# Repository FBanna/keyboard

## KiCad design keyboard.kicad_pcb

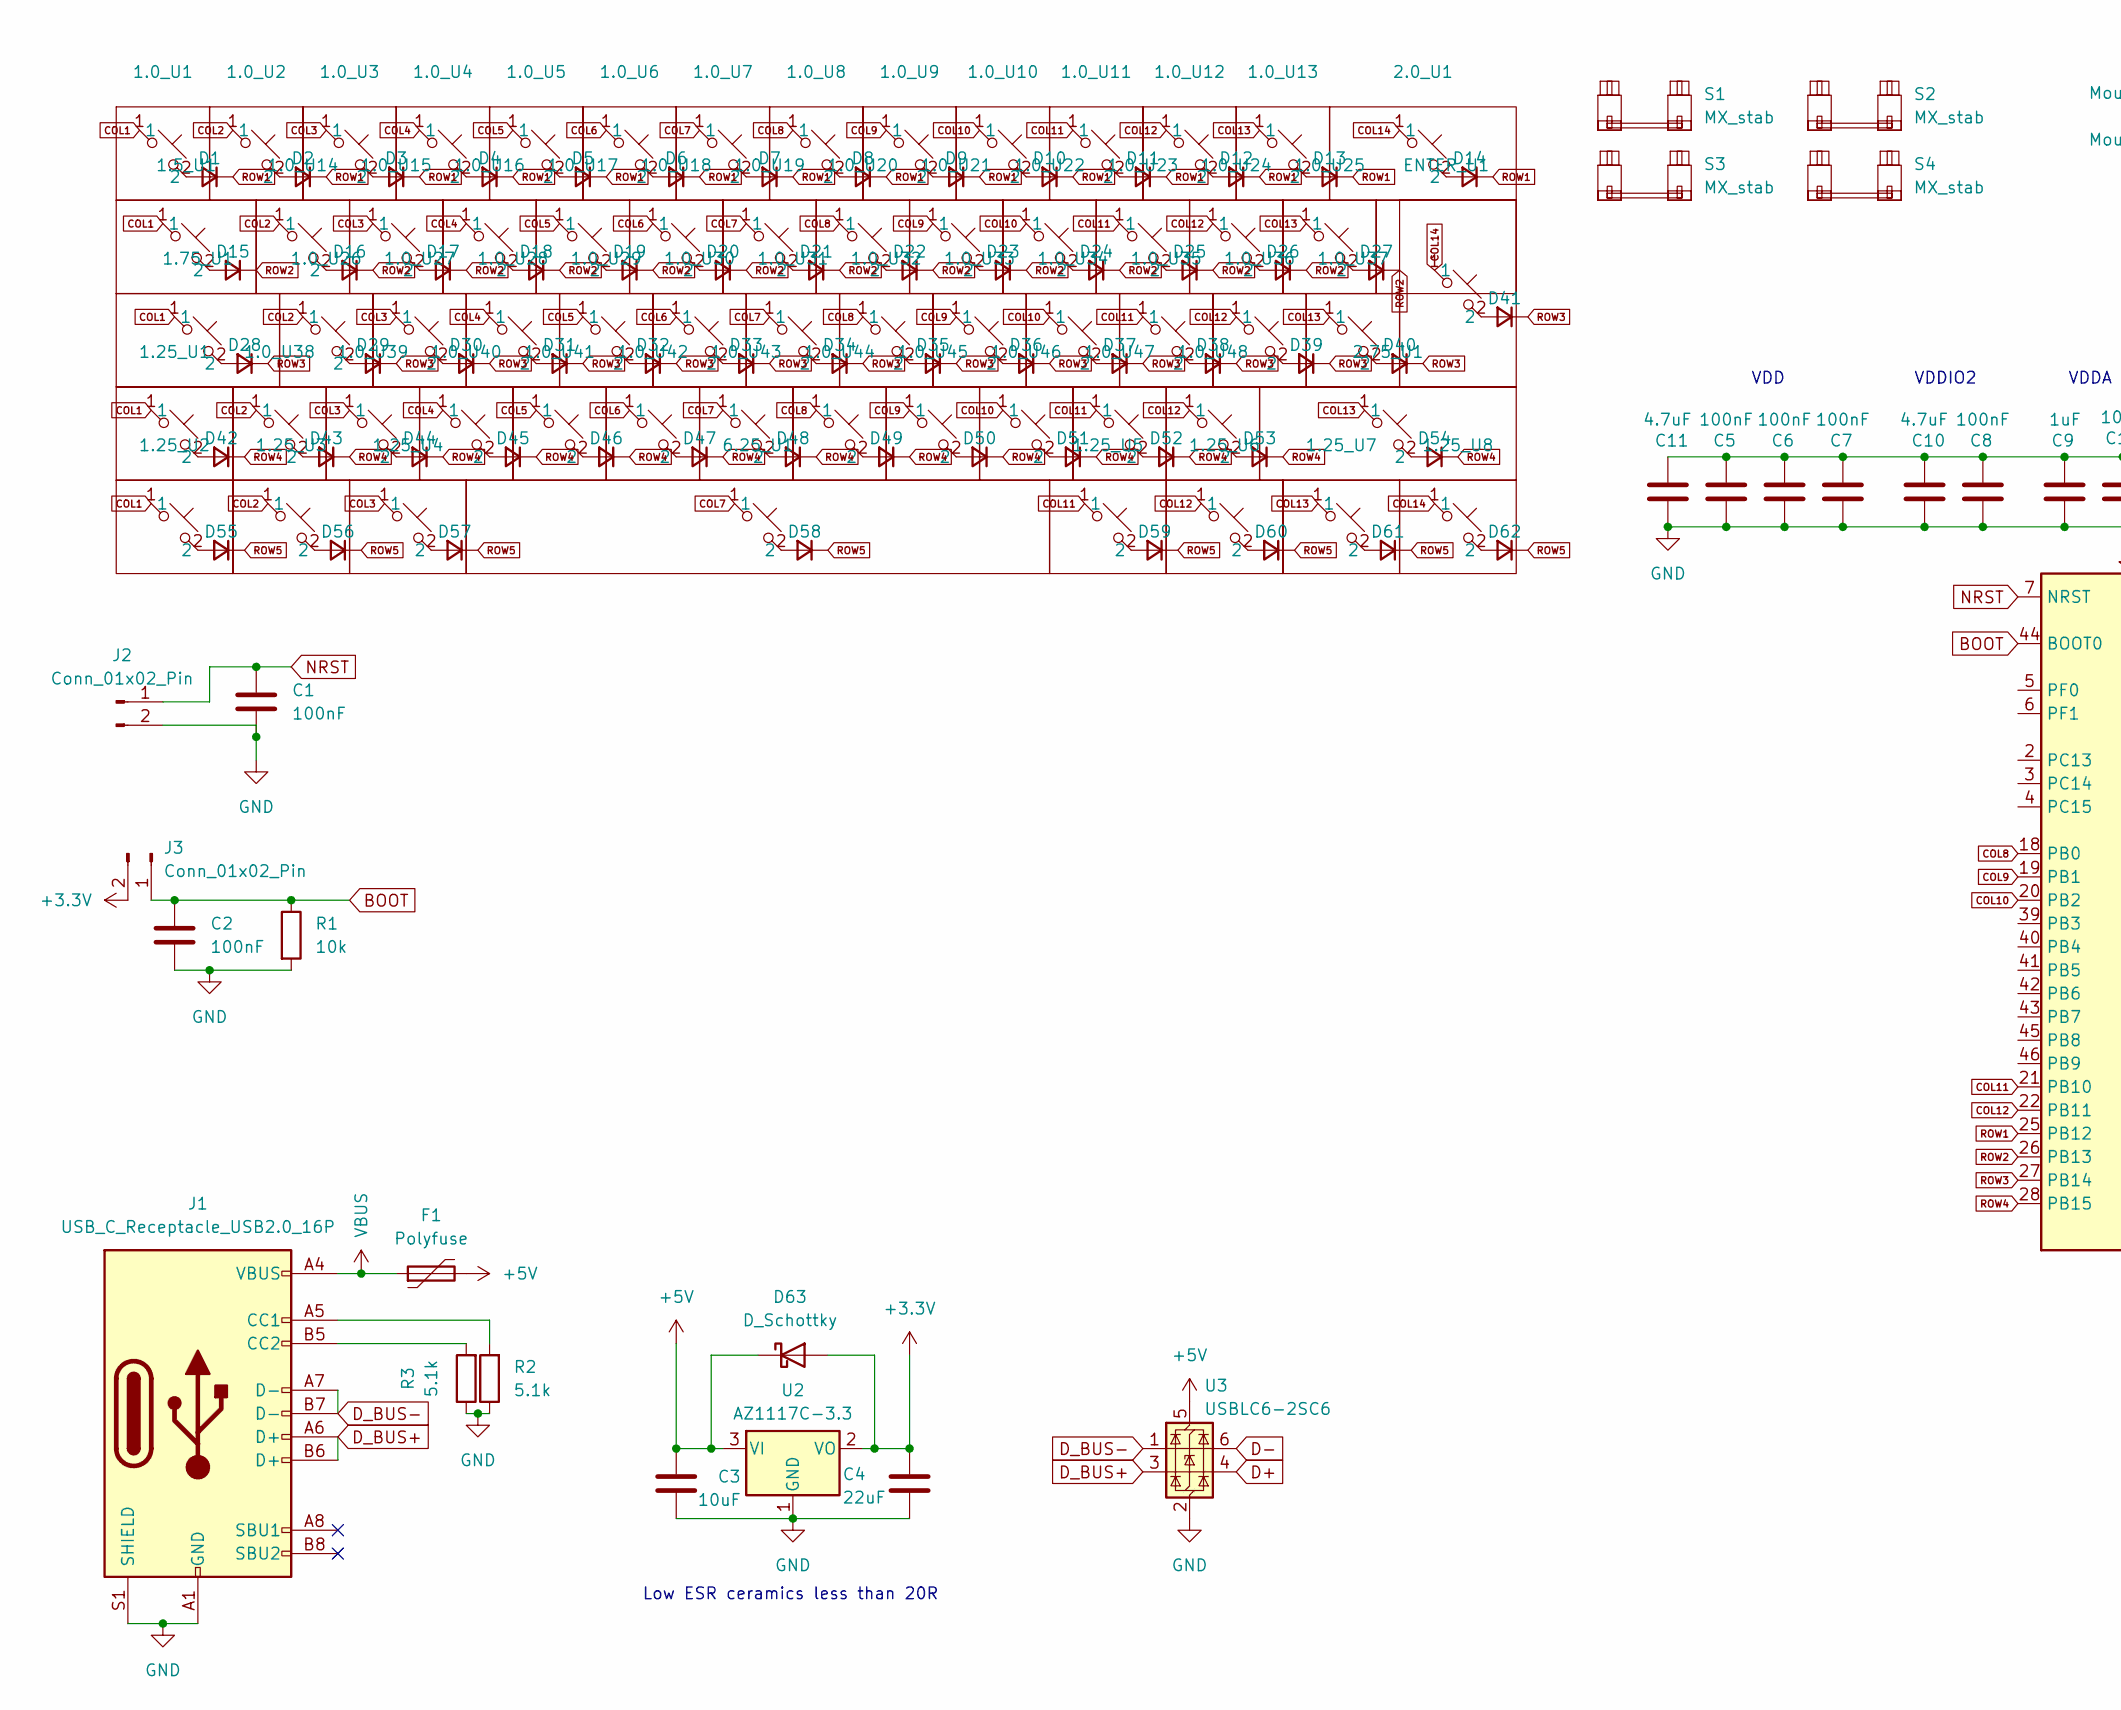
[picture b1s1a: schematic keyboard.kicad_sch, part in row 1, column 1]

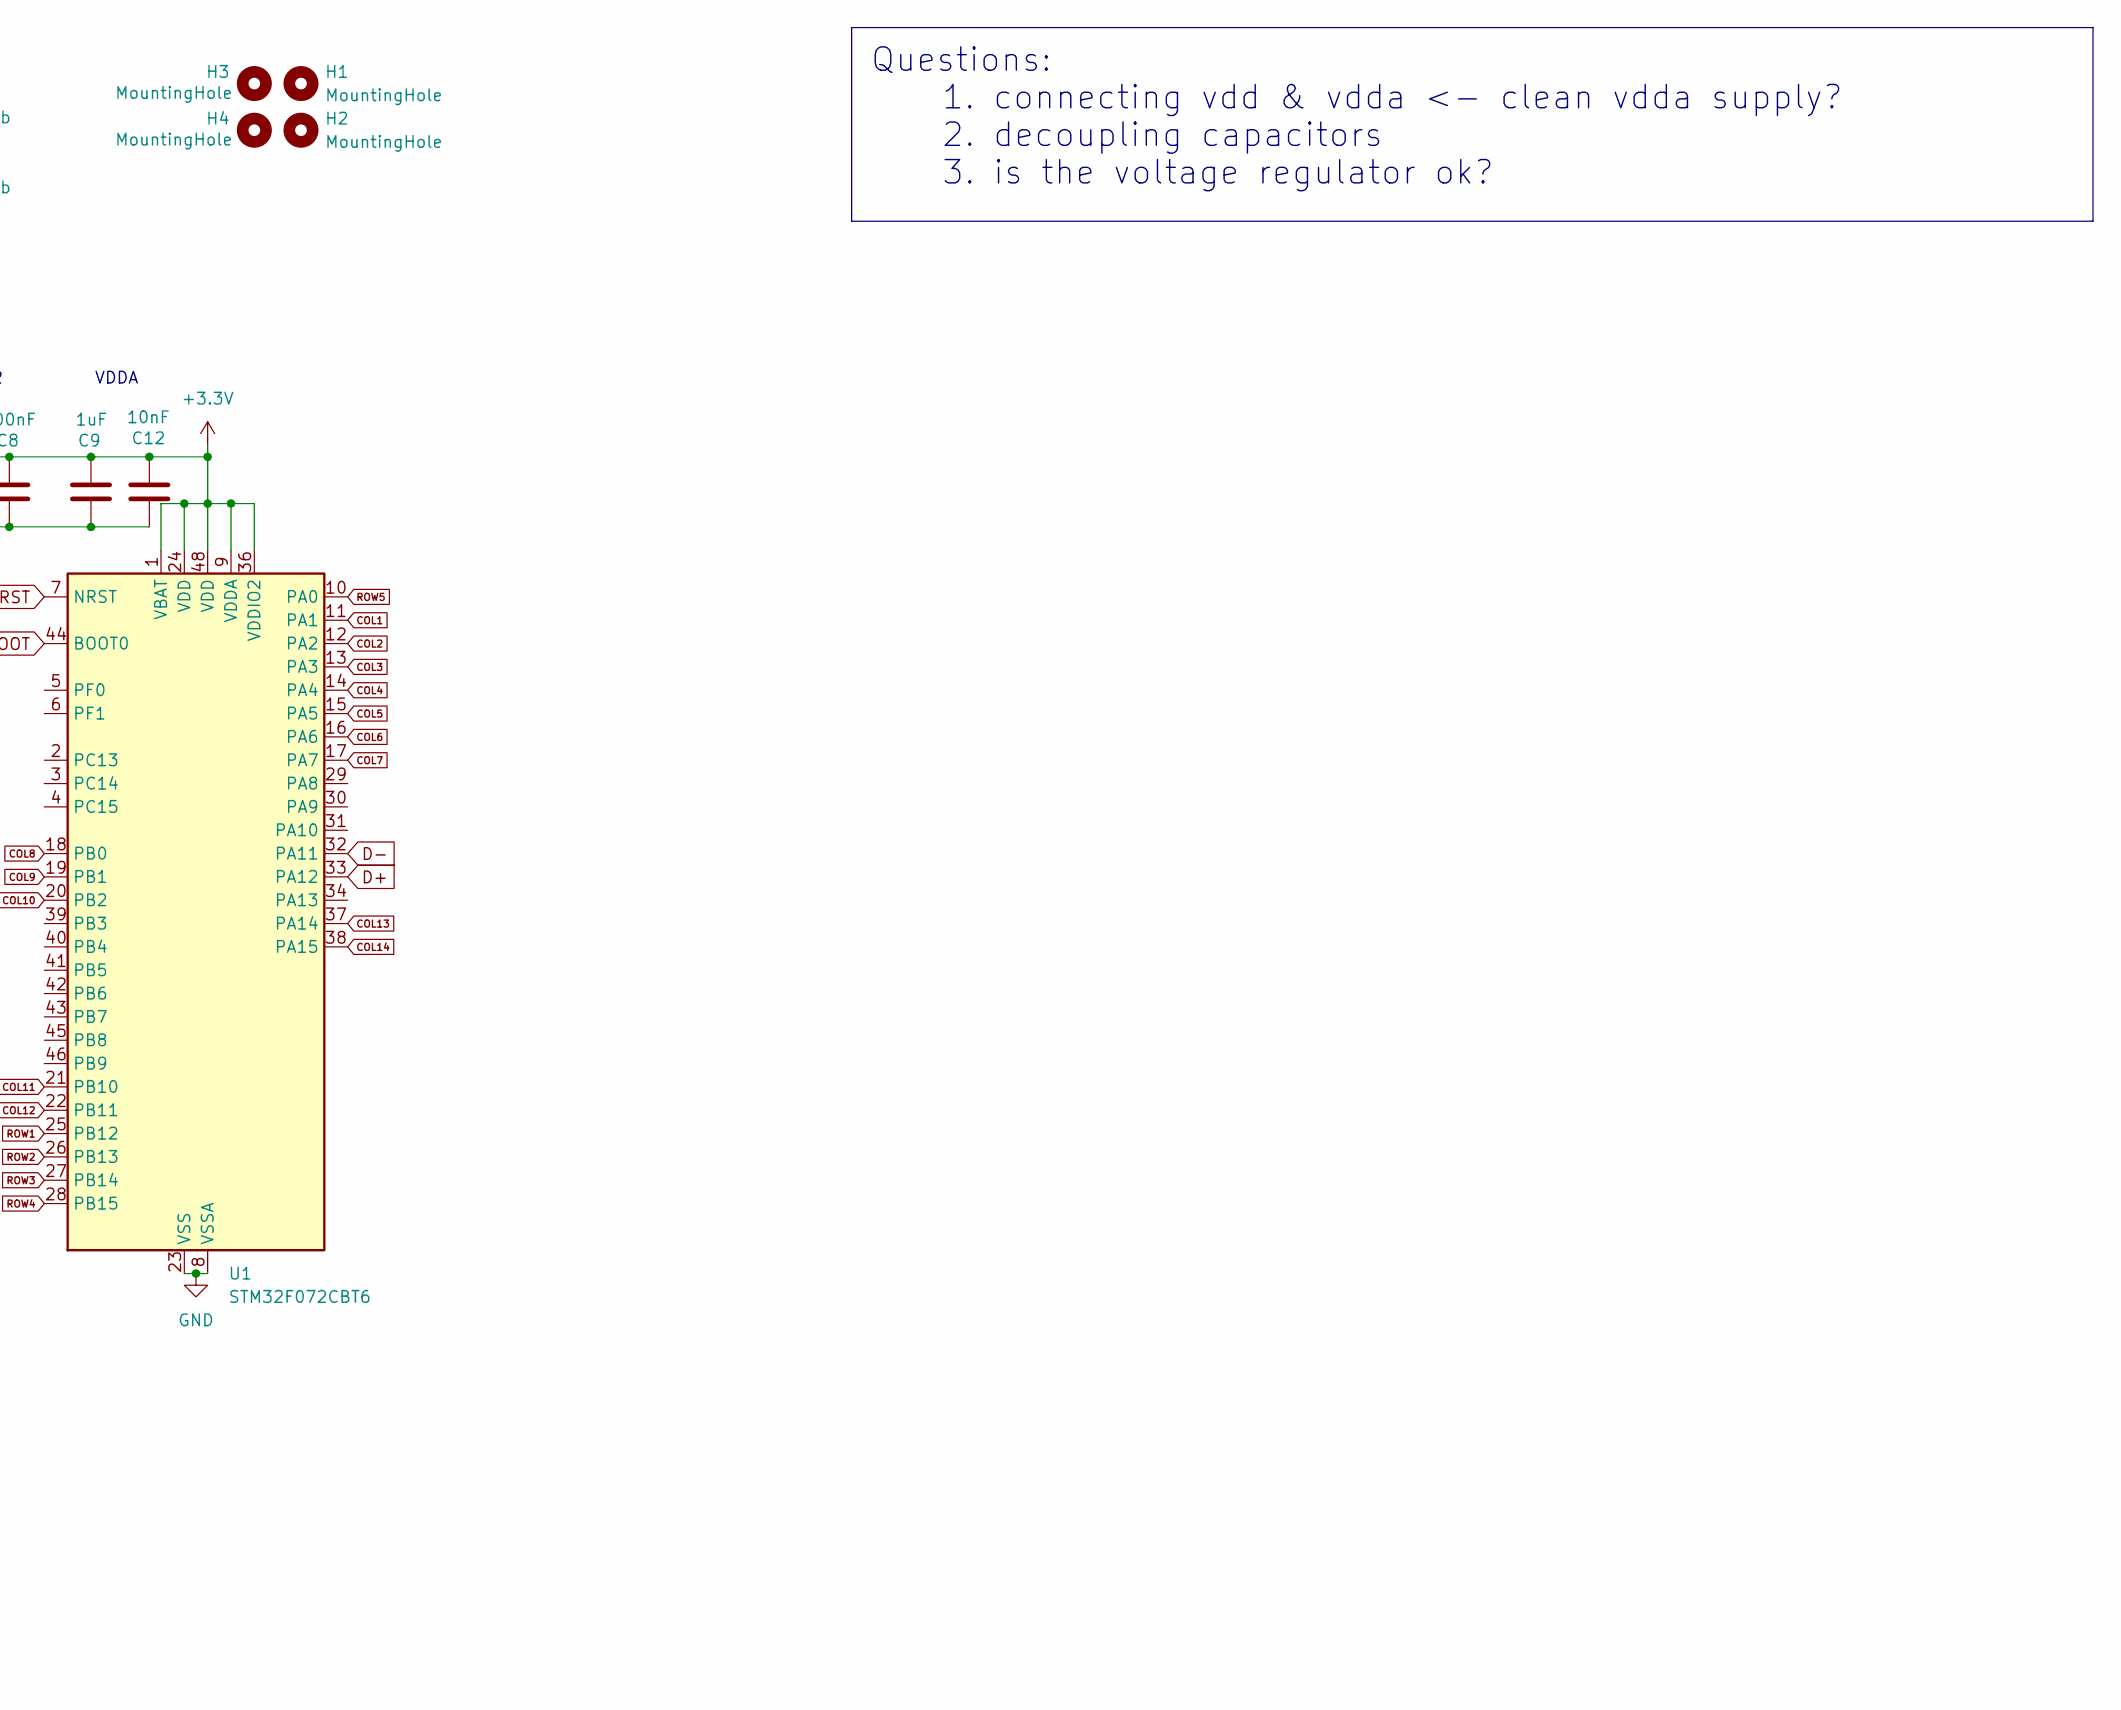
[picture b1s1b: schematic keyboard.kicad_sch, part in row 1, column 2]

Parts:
1.0_U1, 1.0_U2, 1.0_U3, 1.0_U4, 1.0_U5, 1.0_U6, 1.0_U7, 1.0_U8, 1.0_U9, 1.0_U10, 1.0_U11, 1.0_U12, 1.0_U13, 1.0_U14, 1.0_U15, 1.0_U16, 1.0_U17, 1.0_U18, 1.0_U19, 1.0_U20, 1.0_U21, 1.0_U22, 1.0_U23, 1.0_U24, 1.0_U25, 1.0_U26, 1.0_U27, 1.0_U28, 1.0_U29, 1.0_U30, 1.0_U31, 1.0_U32, 1.0_U33, 1.0_U34, 1.0_U35, 1.0_U36, 1.0_U37, 1.0_U38, 1.0_U39, 1.0_U40, 1.0_U41, 1.0_U42, 1.0_U43, 1.0_U44, 1.0_U45, 1.0_U46, 1.0_U47, 1.0_U48: SW_Hotswap_Kailh_MX_1.00u
1.5_U1: SW_Hotswap_Kailh_MX_1.50u
1.25_U1, 1.25_U2, 1.25_U3, 1.25_U4, 1.25_U5, 1.25_U6, 1.25_U7, 1.25_U8: SW_Hotswap_Kailh_MX_1.25u
1.75_U1: SW_Hotswap_Kailh_MX_1.75u
2.0_U1: SW_Hotswap_Kailh_MX_2.00u
2.75_U1: SW_Hotswap_Kailh_MX_2.75u
6.25_U1: SW_Hotswap_Kailh_MX_6.25u
C1, C2, C5, C6, C7, C8: 100nF; C_0402_1005Metric_Pad0.74x0.62mm_HandSolder
C3: 10uF; C_0805_2012Metric_Pad1.18x1.45mm_HandSolder
C4: 22uF; C_0805_2012Metric_Pad1.18x1.45mm_HandSolder
C9: 1uF; C_0805_2012Metric_Pad1.18x1.45mm_HandSolder
C10, C11: 4.7uF; C_0805_2012Metric_Pad1.18x1.45mm_HandSolder
C12: 10nF; C_0402_1005Metric_Pad0.74x0.62mm_HandSolder
D1, D2, D3, D4, D5, D6, D7, D8, D9, D10, D11, D12, D13, D14, D15, D16, D17, D18, D19, D20, D21, D22, D23, D24, D25, D26, D27, D28, D29, D30, D31, D32, D33, D34, D35, D36, D37, D38, D39, D40, D41, D42, D43, D44, D45, D46, D47, D48, D49, D50, D51, D52, D53, D54, D55, D56, D57, D58, D59, D60, D61, D62: D_Small; D_SOD-123F
D63: D_Schottky; D_SOD-123F
ENTER_U1: SW_Hotswap_Kailh_MX_ISOEnter
F1: Polyfuse; Fuse_0805_2012Metric_Pad1.15x1.40mm_HandSolder
H1, H2, H3, H4: MountingHole; MountingHole_3.2mm_M3
J1: USB_C_Receptacle_USB2.0_16P; USB_C_Receptacle_Palconn_UTC16-G
J2, J3: Conn_01x02_Pin; PinHeader_1x02_P2.54mm_Vertical
R1: 10k; R_0402_1005Metric_Pad0.72x0.64mm_HandSolder
R2, R3: 5.1k; R_0402_1005Metric_Pad0.72x0.64mm_HandSolder
S1: MX_stab; STAB_MX_P_6.25u
S2: MX_stab; STAB_MX_P_ISO
S3: MX_stab; STAB_MX_P_2u
S4: MX_stab; STAB_MX_2.75u
U1: STM32F072CBT6; LQFP-48_7x7mm_P0.5mm
U2: AZ1117C-3.3; SOT-89-3_Handsoldering
U3: USBLC6-2SC6; SOT-23-6

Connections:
+3.3V: C4.1, C5.1, C6.1, C7.1, C8.1, C9.1, C10.1, C11.1, C12.1, D63.2 (A), J3.2, U1.1 (VBAT), U1.9 (VDDA), U1.24 (VDD), U1.36 (VDDIO2), U1.48 (VDD), U2.2 (VO)
+5V: C3.2, D63.1 (K), F1.2, U2.3 (VI), U3.5 (VBUS)
BOOT: C2.1, J3.1, R1.1, U1.44 (BOOT0)
COL1: 1.0_U1.1, 1.5_U1.1, 1.25_U1.1, 1.25_U2.1, 1.75_U1.1, U1.11 (PA1)
COL2: 1.0_U2.1, 1.0_U14.1, 1.0_U26.1, 1.0_U38.1, 1.25_U3.1, U1.12 (PA2)
COL3: 1.0_U3.1, 1.0_U15.1, 1.0_U27.1, 1.0_U39.1, 1.25_U4.1, U1.13 (PA3)
COL4: 1.0_U4.1, 1.0_U16.1, 1.0_U28.1, 1.0_U40.1, U1.14 (PA4)
COL5: 1.0_U5.1, 1.0_U17.1, 1.0_U29.1, 1.0_U41.1, U1.15 (PA5)
COL6: 1.0_U6.1, 1.0_U18.1, 1.0_U30.1, 1.0_U42.1, U1.16 (PA6)
COL7: 1.0_U7.1, 1.0_U19.1, 1.0_U31.1, 1.0_U43.1, 6.25_U1.1, U1.17 (PA7)
COL8: 1.0_U8.1, 1.0_U20.1, 1.0_U32.1, 1.0_U44.1, U1.18 (PB0)
COL9: 1.0_U9.1, 1.0_U21.1, 1.0_U33.1, 1.0_U45.1, U1.19 (PB1)
COL10: 1.0_U10.1, 1.0_U22.1, 1.0_U34.1, 1.0_U46.1, U1.20 (PB2)
COL11: 1.0_U11.1, 1.0_U23.1, 1.0_U35.1, 1.0_U47.1, 1.25_U5.1, U1.21 (PB10)
COL12: 1.0_U12.1, 1.0_U24.1, 1.0_U36.1, 1.0_U48.1, 1.25_U6.1, U1.22 (PB11)
COL13: 1.0_U13.1, 1.0_U25.1, 1.0_U37.1, 1.25_U7.1, 2.75_U1.1, U1.37 (PA14)
COL14: 1.25_U8.1, 2.0_U1.1, ENTER_U1.1, U1.38 (PA15)
D+: U1.33 (PA12), U3.4 (I/O2)
D-: U1.32 (PA11), U3.6 (I/O1)
D_BUS+: J1.A6 (D+), J1.B6 (D+), U3.3 (I/O2)
D_BUS-: J1.A7 (D-), J1.B7 (D-), U3.1 (I/O1)
GND: C1.2, C2.2, C3.1, C4.2, C5.2, C6.2, C7.2, C8.2, C9.2, C10.2, C11.2, C12.2, J1.A1 (GND), J1.A12 (GND), J1.B1 (GND), J1.B12 (GND), J1.S1 (SHIELD), J2.2, R1.2, R2.1, R3.1, U1.8 (VSSA), U1.23 (VSS), U1.35 (VSS), U1.47 (VSS), U2.1 (GND), U3.2 (GND)
NRST: C1.1, J2.1, U1.7 (NRST)
unnamed: 1.0_U1.2, D1.2 (A)
unnamed: 1.0_U2.2, D2.2 (A)
unnamed: 1.0_U3.2, D3.2 (A)
unnamed: 1.0_U4.2, D4.2 (A)
unnamed: 1.0_U5.2, D5.2 (A)
unnamed: 1.0_U6.2, D6.2 (A)
unnamed: 1.0_U7.2, D7.2 (A)
unnamed: 1.0_U8.2, D8.2 (A)
unnamed: 1.0_U9.2, D9.2 (A)
unnamed: 1.0_U10.2, D10.2 (A)
unnamed: 1.0_U11.2, D11.2 (A)
unnamed: 1.0_U12.2, D12.2 (A)
unnamed: 1.0_U13.2, D13.2 (A)
unnamed: 2.0_U1.2, D14.2 (A)
unnamed: 1.5_U1.2, D15.2 (A)
unnamed: 1.0_U14.2, D16.2 (A)
unnamed: 1.0_U15.2, D17.2 (A)
unnamed: 1.0_U16.2, D18.2 (A)
unnamed: 1.0_U17.2, D19.2 (A)
unnamed: 1.0_U18.2, D20.2 (A)
unnamed: 1.0_U19.2, D21.2 (A)
unnamed: 1.0_U20.2, D22.2 (A)
unnamed: 1.0_U21.2, D23.2 (A)
unnamed: 1.0_U22.2, D24.2 (A)
unnamed: 1.0_U23.2, D25.2 (A)
unnamed: 1.0_U24.2, D26.2 (A)
unnamed: 1.0_U25.2, D27.2 (A)
unnamed: 1.75_U1.2, D28.2 (A)
unnamed: 1.0_U26.2, D29.2 (A)
unnamed: 1.0_U27.2, D30.2 (A)
unnamed: 1.0_U28.2, D31.2 (A)
unnamed: 1.0_U29.2, D32.2 (A)
unnamed: 1.0_U30.2, D33.2 (A)
unnamed: 1.0_U31.2, D34.2 (A)
unnamed: 1.0_U32.2, D35.2 (A)
unnamed: 1.0_U33.2, D36.2 (A)
unnamed: 1.0_U34.2, D37.2 (A)
unnamed: 1.0_U35.2, D38.2 (A)
unnamed: 1.0_U36.2, D39.2 (A)
unnamed: 1.0_U37.2, D40.2 (A)
unnamed: D41.2 (A), ENTER_U1.2
unnamed: 1.25_U1.2, D42.2 (A)
unnamed: 1.0_U38.2, D43.2 (A)
unnamed: 1.0_U39.2, D44.2 (A)
unnamed: 1.0_U40.2, D45.2 (A)
unnamed: 1.0_U41.2, D46.2 (A)
unnamed: 1.0_U42.2, D47.2 (A)
unnamed: 1.0_U43.2, D48.2 (A)
unnamed: 1.0_U44.2, D49.2 (A)
unnamed: 1.0_U45.2, D50.2 (A)
unnamed: 1.0_U46.2, D51.2 (A)
unnamed: 1.0_U47.2, D52.2 (A)
unnamed: 1.0_U48.2, D53.2 (A)
unnamed: 2.75_U1.2, D54.2 (A)
unnamed: 1.25_U2.2, D55.2 (A)
unnamed: 1.25_U3.2, D56.2 (A)
unnamed: 1.25_U4.2, D57.2 (A)
unnamed: 6.25_U1.2, D58.2 (A)
unnamed: 1.25_U5.2, D59.2 (A)
unnamed: 1.25_U6.2, D60.2 (A)
unnamed: 1.25_U7.2, D61.2 (A)
unnamed: 1.25_U8.2, D62.2 (A)
unnamed: J1.A5 (CC1), R2.2
unnamed: J1.B5 (CC2), R3.2
ROW1: D1.1 (K), D2.1 (K), D3.1 (K), D4.1 (K), D5.1 (K), D6.1 (K), D7.1 (K), D8.1 (K), D9.1 (K), D10.1 (K), D11.1 (K), D12.1 (K), D13.1 (K), D14.1 (K), U1.25 (PB12)
ROW2: D15.1 (K), D16.1 (K), D17.1 (K), D18.1 (K), D19.1 (K), D20.1 (K), D21.1 (K), D22.1 (K), D23.1 (K), D24.1 (K), D25.1 (K), D26.1 (K), D27.1 (K), U1.26 (PB13)
ROW3: D28.1 (K), D29.1 (K), D30.1 (K), D31.1 (K), D32.1 (K), D33.1 (K), D34.1 (K), D35.1 (K), D36.1 (K), D37.1 (K), D38.1 (K), D39.1 (K), D40.1 (K), D41.1 (K), U1.27 (PB14)
ROW4: D42.1 (K), D43.1 (K), D44.1 (K), D45.1 (K), D46.1 (K), D47.1 (K), D48.1 (K), D49.1 (K), D50.1 (K), D51.1 (K), D52.1 (K), D53.1 (K), D54.1 (K), U1.28 (PB15)
ROW5: D55.1 (K), D56.1 (K), D57.1 (K), D58.1 (K), D59.1 (K), D60.1 (K), D61.1 (K), D62.1 (K), U1.10 (PA0)
VBUS: F1.1, J1.A4 (VBUS), J1.A9 (VBUS), J1.B4 (VBUS), J1.B9 (VBUS)

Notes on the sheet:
Questions: 1. connecting vdd & vdda <- clean vdda supply? 2. decoupling capacitors 3. is the voltage regulator ok?
VDD
VDDA
VDDIO2
Low ESR ceramics less than 20R

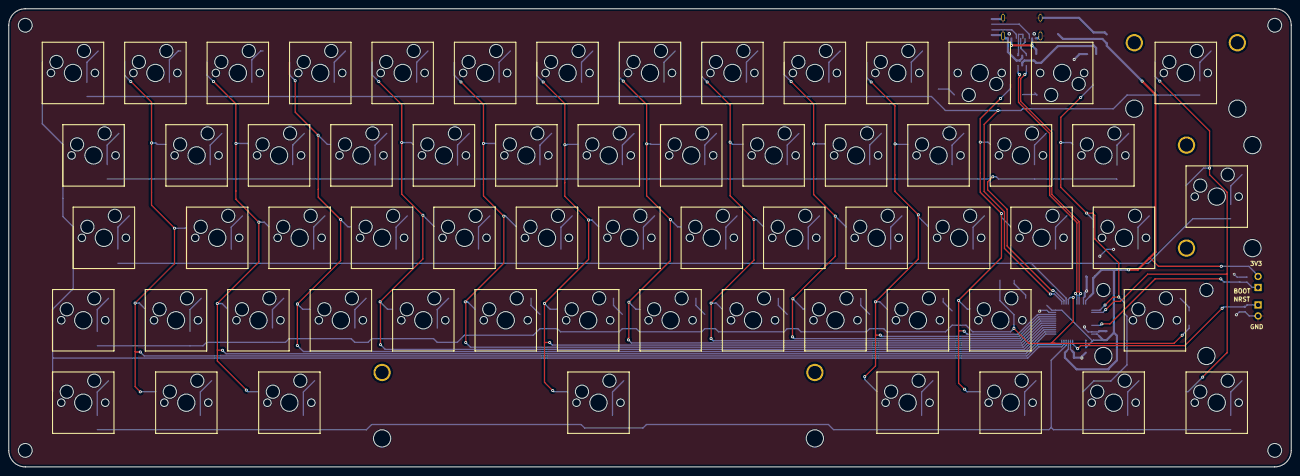
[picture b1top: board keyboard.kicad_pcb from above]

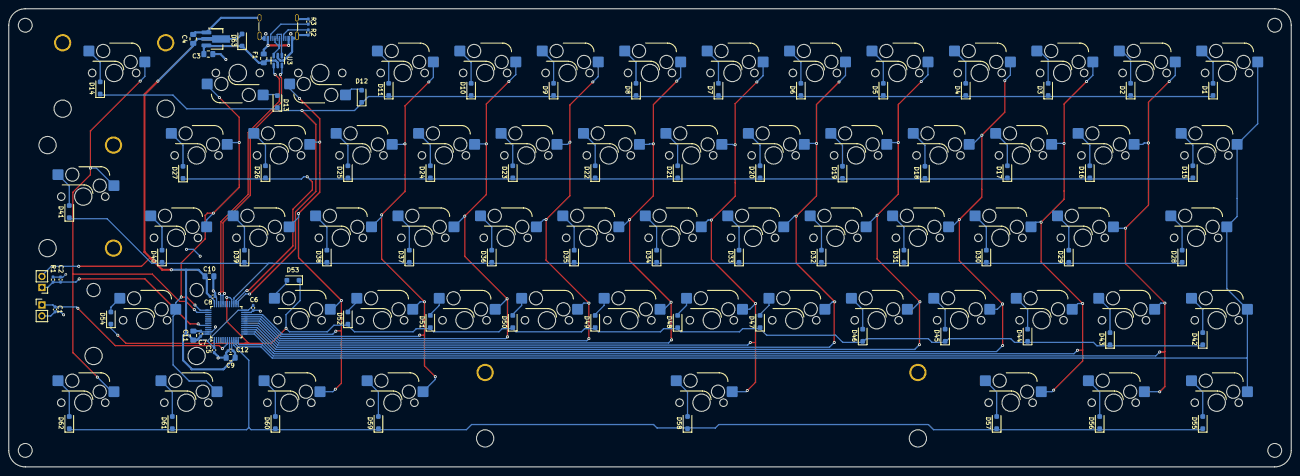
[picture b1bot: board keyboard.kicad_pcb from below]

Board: 2 copper layers, 296.4 x 105.9 mm, 155 parts (85 on the bottom side), 93 nets.

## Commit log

2024-08-08 init
2024-08-31 finished????!!??
